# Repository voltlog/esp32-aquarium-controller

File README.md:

# ESP32 Aquarium/Terarrium Controller

This project started when a friend of mine which has a snake terrarium asked for my help to build a system that is capable of regulating temperature and humidity so the snake can live in optimum conditions. I’m not necessarily a snake lover, I would rather stay away from these kinds of creatures but that doesn’t stop me from helping my friend.

The ESP32 module is the core of this board and it serves as a central processor taking in sensor data and deciding when to switch on/off the 4 relay controlled outputs to adjust the environment inside the aquarium/terrarium.

If you would like to order one of these boards ready assembled, check out my [Tindie store](https://www.tindie.com/products/voltlog/esp32-aquarium-terrarium-controller/).

More info about this project in [Voltlog #361](https://youtu.be/Hlmbx2yu9M0).

Known issues in revA:
- Power brick module footprint is wrong so it needs to be installed on the bottom side of the board. 
- There are no mounting holes.
- Fitting the board inside the intended enclosure required some adjustments on the round cutouts. This is something to consider if you want to use the same enclosure but if you plan to install this in a larger plastic enclosure, it shouldn't be a problem.

## Firmware
Firmware is built as a PlatformIO project on the Arduino platform using publicly available open-source libraries. The HTML page servered by the asyncronous web server needs to be loaded into the ESP32 SPIFFS memory using the standard upload procedure. The code is just a proof of concept and is provided AS IS without warranty of any kind.

## Safety Warning
This control board uses mains voltage so you need to know what you are doing, otherwise, there is a high risk of electrical shock and/or fire. This is a serious topic, if you are not sure what you are doing, ask for help from an electrician. Every connection should be double checked before applying mains power.

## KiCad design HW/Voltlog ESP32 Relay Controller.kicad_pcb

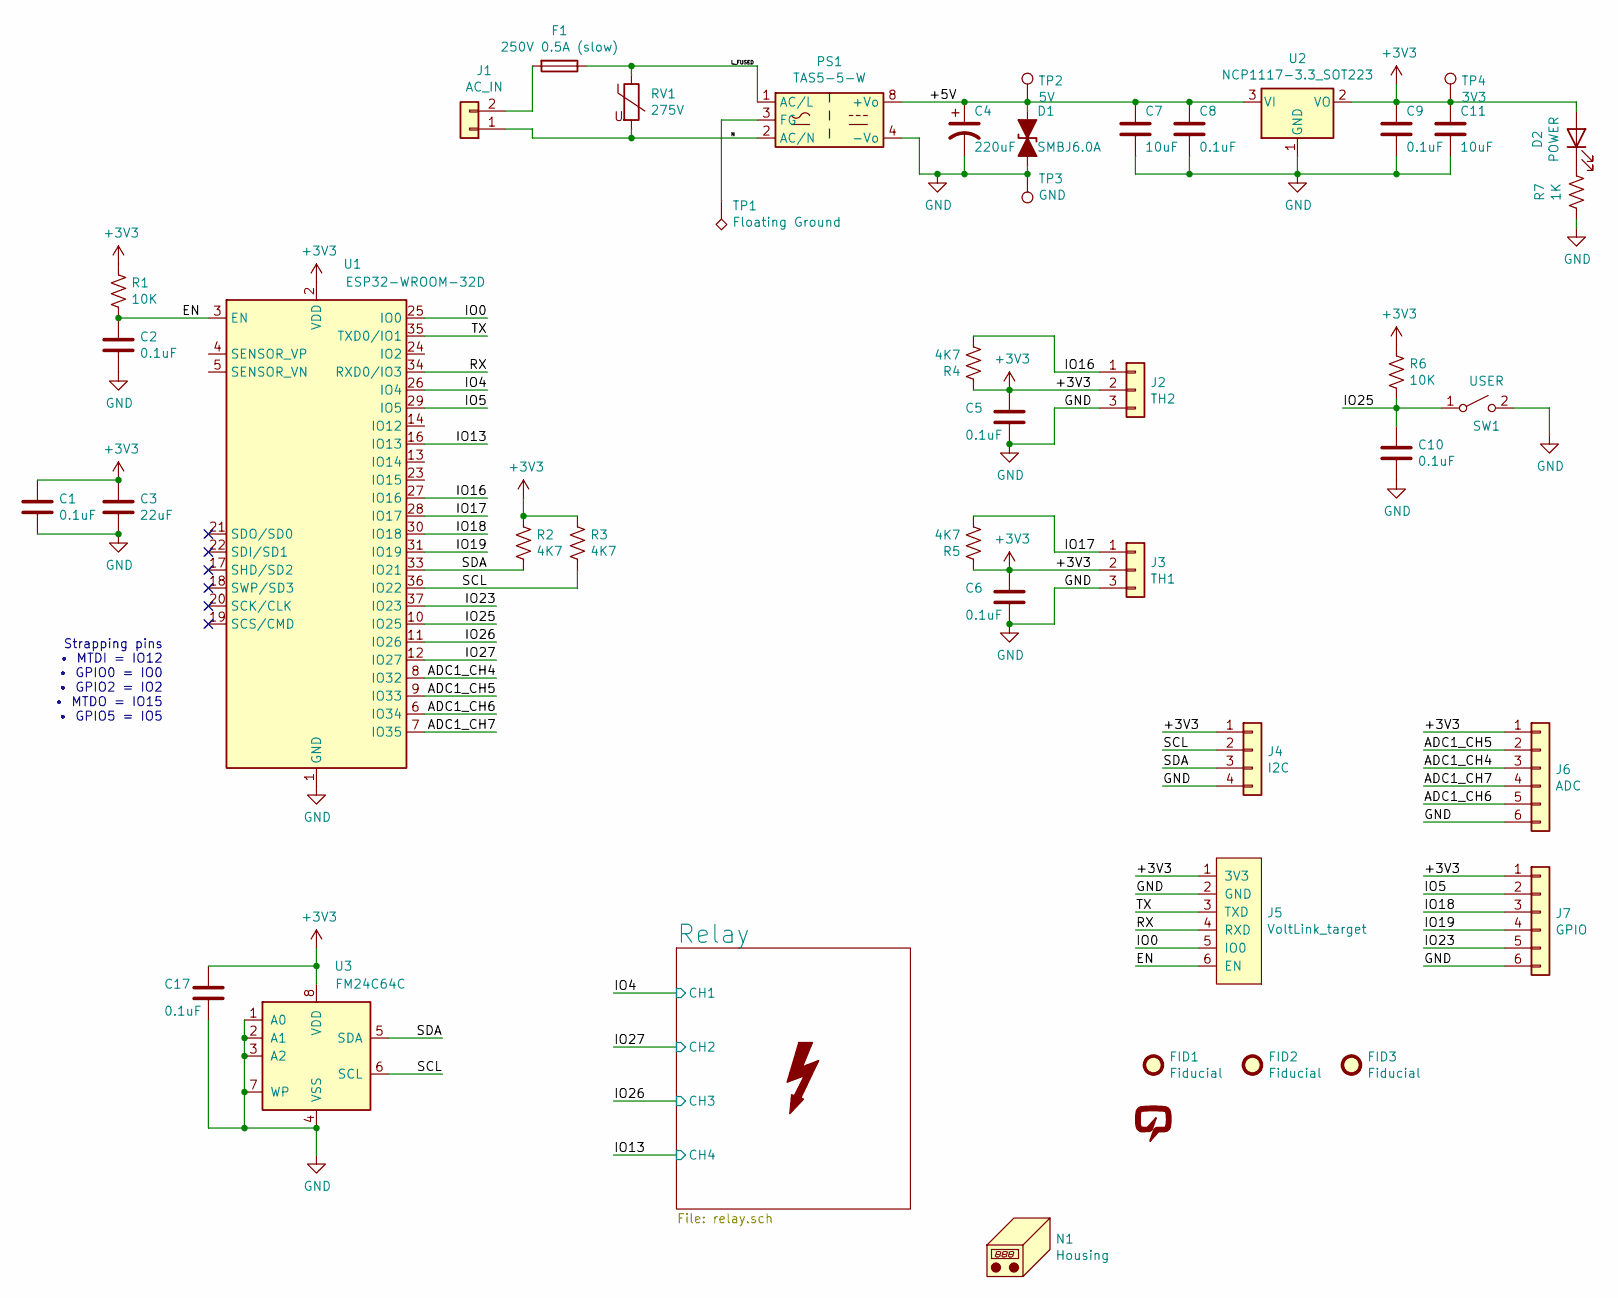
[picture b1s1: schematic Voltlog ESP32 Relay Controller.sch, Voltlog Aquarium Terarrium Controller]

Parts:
C1, C2, C5, C6, C8, C9, C10, C17: 0.1uF; C_0805_2012Metric
C3: 22uF; C_1206_3216Metric
C4: 220uF; CP_Elec_8x10.5; Voltage 25V
C7, C11: 10uF; C_0805_2012Metric
D1: SMBJ6.0A; D_SMB
D2: POWER; LED_0805_2012Metric
F1: 250V 0.5A (slow); Fuseholder_Cylinder-5x20mm_Stelvio-Kontek_PTF78_Horizontal_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
FID1, FID2, FID3: Fiducial; Fiducial_0.5mm_Mask1mm
J1: AC_IN; TerminalBlock_RND_205-00287_1x02_P5.08mm_Horizontal
J2: TH2; TerminalBlock_RND_205-00233_1x03_P5.08mm_Horizontal
J3: TH1; TerminalBlock_RND_205-00233_1x03_P5.08mm_Horizontal
J4: I2C; PinHeader_1x04_P2.54mm_Vertical
J5: VoltLink_target; VoltLink
J6: ADC; PinHeader_1x06_P2.54mm_Vertical
J7: GPIO; PinHeader_1x06_P2.54mm_Vertical
N1: Housing; Bernic_BE4969842011
PS1: TAS5-5-W; TDPOWER-TAS5
R1, R6: 10K; R_0805_2012Metric
R2, R3, R4, R5: 4K7; R_0805_2012Metric
R7: 1K; R_0805_2012Metric
RV1: 275V; RV_Disc_D12mm_W5mm_P7.5mm
SW1: USER; SW_SPST_PTS645
TP1: Floating Ground; SolderWirePad_1x01_SMD_5x10mm
TP2: 5V; TestPoint_Pad_D1.0mm
TP3: GND; TestPoint_Pad_D1.0mm
TP4: 3V3; TestPoint_Pad_D1.0mm
U1: ESP32-WROOM-32D; ESP32-WROOM-32
U2: NCP1117-3.3_SOT223; SOT-223-3_TabPin2
U3: FM24C64C; SOIC-8_3.9x4.9mm_P1.27mm
V1: VOLTLOG_LOGO; voltlog_mask_5mm

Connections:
+3V3: C1.1, C3.1, C5.1, C6.1, C9.1, C11.1, C17.1, D2.2 (A), J2.2, J3.2, J4.1, J5.1 (3V3), J6.1, J7.1, R1.1, R2.1, R3.1, R4.1, R5.1, R6.1, TP4.1, U1.2 (VDD), U2.2 (VO), U3.8 (VDD)
+5V: C4.1, C7.1, C8.1, D1.1 (A1), PS1.8 (+Vo), TP2.1, U2.3 (VI); also elsewhere on the board
/ADC1_CH4: J6.3, U1.8 (IO32)
/ADC1_CH5: J6.2, U1.9 (IO33)
/ADC1_CH6: J6.5, U1.6 (IO34)
/ADC1_CH7: J6.4, U1.7 (IO35)
/EN: C2.1, J5.6 (EN), R1.2, U1.3 (EN)
/IO0: J5.5 (IO0), U1.25 (IO0)
/IO2: U1.24 (IO2)
/IO4: U1.26 (IO4); also elsewhere on the board
/IO5: J7.2, U1.29 (IO5)
/IO13: U1.16 (IO13); also elsewhere on the board
/IO16: J2.1, R4.2, U1.27 (IO16)
/IO17: J3.1, R5.2, U1.28 (IO17)
/IO18: J7.3, U1.30 (IO18)
/IO19: J7.4, U1.31 (IO19)
/IO23: J7.5, U1.37 (IO23)
/IO25: C10.1, R6.2, SW1.1 (A), U1.10 (IO25)
/IO26: U1.11 (IO26); also elsewhere on the board
/IO27: U1.12 (IO27); also elsewhere on the board
/L_FUSED: F1.1, PS1.1 (AC/L), RV1.1
/N: J1.1, PS1.2 (AC/N), RV1.2
/RX: J5.4 (RXD), U1.34 (RXD0/IO3)
/SCL: J4.2, R3.2, U1.36 (IO22), U3.6 (SCL)
/SDA: J4.3, R2.2, U1.33 (IO21), U3.5 (SDA)
/TX: J5.3 (TXD), U1.35 (TXD0/IO1)
GND: C1.2, C2.2, C3.2, C4.2, C5.2, C6.2, C7.2, C8.2, C9.2, C10.2, C11.2, C17.2, D1.2 (A2), J2.3, J3.3, J4.4, J5.2 (GND), J6.6, J7.6, PS1.4 (-Vo), R7.2, SW1.2 (B), TP3.1, U1.1 (GND), U1.15 (GND), U1.38 (GND), U1.39 (GND), U2.1 (GND), U3.1 (A0), U3.2 (A1), U3.3 (A2), U3.4 (VSS), U3.7 (WP); also elsewhere on the board
unnamed: D2.1 (K), R7.1
unnamed: F1.2, J1.2
unnamed: PS1.3 (FG), TP1.1

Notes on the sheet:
Strapping pins • MTDI = IO12 • GPIO0 = IO0 • GPIO2 = IO2 • MTDO = IO15 • GPIO5 = IO5

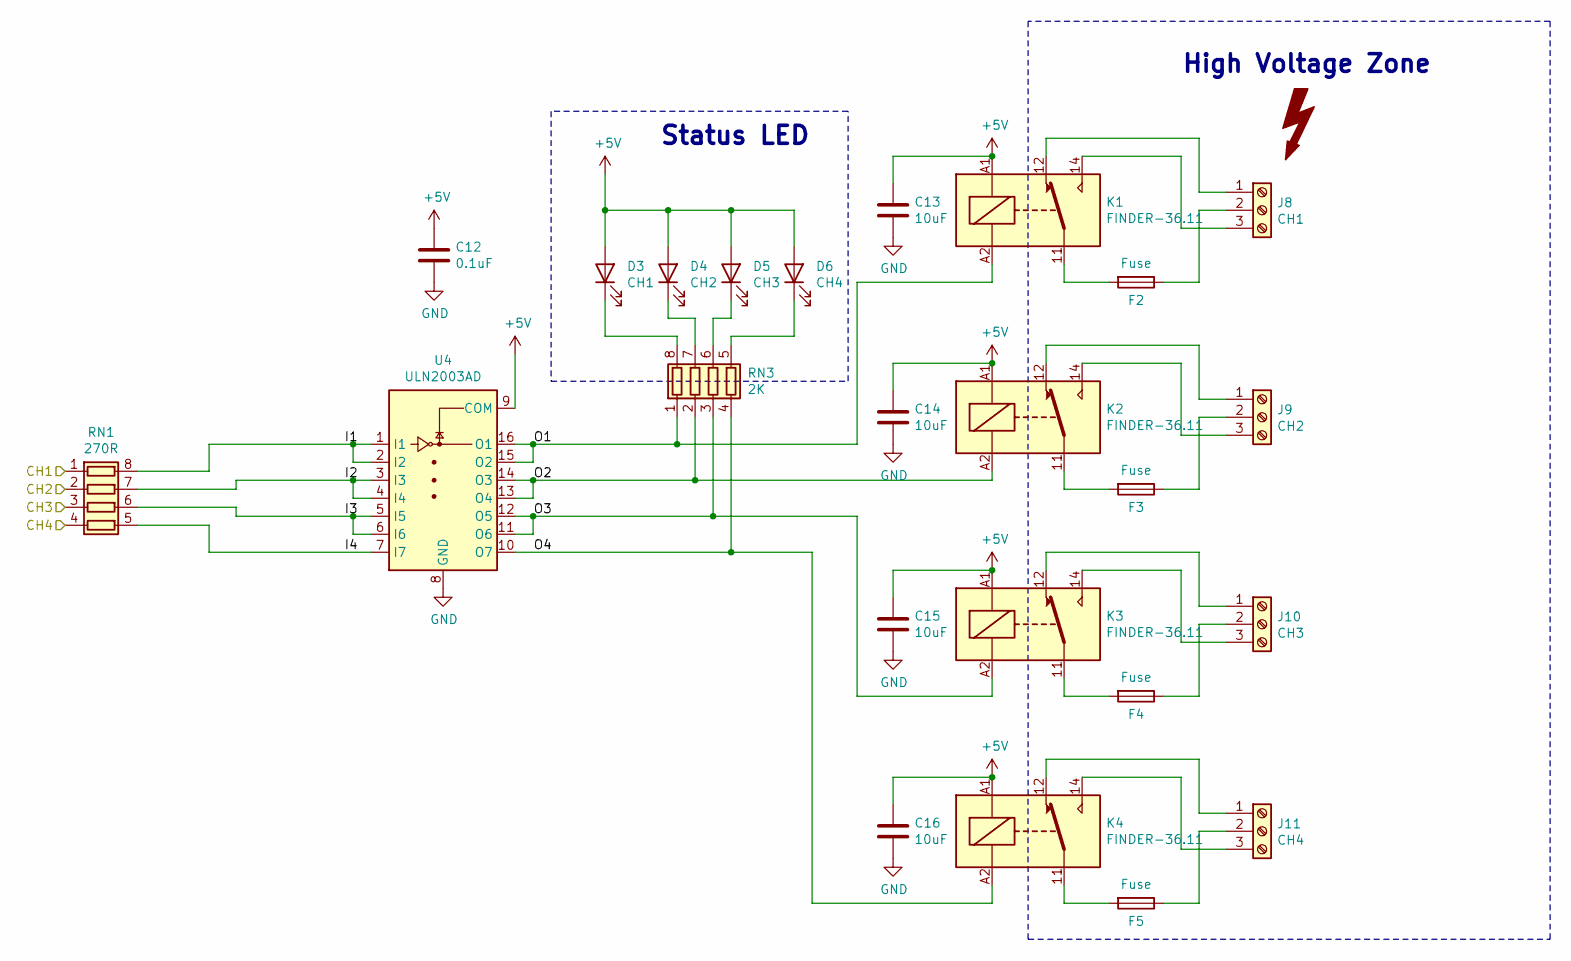
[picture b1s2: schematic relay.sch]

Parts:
C12: 0.1uF; C_0805_2012Metric
C13, C14, C15, C16: 10uF; C_0805_2012Metric
D3: CH1; LED_0805_2012Metric
D4: CH2; LED_0805_2012Metric
D5: CH3; LED_0805_2012Metric
D6: CH4; LED_0805_2012Metric
F2, F3, F4, F5: Fuse; Fuseholder_Cylinder-5x20mm_Stelvio-Kontek_PTF78_Horizontal_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
J8: CH1; TerminalBlock_Phoenix_MKDS-3-3-5.08_1x03_P5.08mm_Horizontal
J9: CH2; TerminalBlock_Phoenix_MKDS-3-3-5.08_1x03_P5.08mm_Horizontal
J10: CH3; TerminalBlock_Phoenix_MKDS-3-3-5.08_1x03_P5.08mm_Horizontal
J11: CH4; TerminalBlock_Phoenix_MKDS-3-3-5.08_1x03_P5.08mm_Horizontal
K1, K2, K3, K4: FINDER-36.11; Relay_SPDT_Finder_36.11
RN1: 270R; R_Array_Convex_4x0603
RN3: 2K; R_Array_Convex_4x0603
U4: ULN2003AD; SO-16_3.9x9.9mm_P1.27mm

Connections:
+5V: C12.1, C13.2, C14.2, C15.2, C16.2, D3.2 (A), D4.2 (A), D5.2 (A), D6.2 (A), K1.A1, K2.A1, K3.A1, K4.A1, U4.9 (COM); also elsewhere on the board
/IO4: RN1.1 (R1.1); also elsewhere on the board
/IO13: RN1.4 (R4.1); also elsewhere on the board
/IO26: RN1.3 (R3.1); also elsewhere on the board
/IO27: RN1.2 (R2.1); also elsewhere on the board
/Relay/I1: RN1.8 (R1.2), U4.1 (I1), U4.2 (I2)
/Relay/I2: RN1.7 (R2.2), U4.3 (I3), U4.4 (I4)
/Relay/I3: RN1.6 (R3.2), U4.5 (I5), U4.6 (I6)
/Relay/I4: RN1.5 (R4.2), U4.7 (I7)
/Relay/O1: K1.A2, RN3.1 (R1.1), U4.15 (O2), U4.16 (O1)
/Relay/O2: K2.A2, RN3.2 (R2.1), U4.13 (O4), U4.14 (O3)
/Relay/O3: K3.A2, RN3.3 (R3.1), U4.11 (O6), U4.12 (O5)
/Relay/O4: K4.A2, RN3.4 (R4.1), U4.10 (O7)
GND: C12.2, C13.1, C14.1, C15.1, C16.1, U4.8 (GND); also elsewhere on the board
unnamed: D3.1 (K), RN3.8 (R1.2)
unnamed: D4.1 (K), RN3.7 (R2.2)
unnamed: D5.1 (K), RN3.6 (R3.2)
unnamed: D6.1 (K), RN3.5 (R4.2)
unnamed: F2.1, J8.2
unnamed: F2.2, K1.11
unnamed: F3.1, J9.2
unnamed: F3.2, K2.11
unnamed: F4.1, J10.2
unnamed: F4.2, K3.11
unnamed: F5.1, J11.2
unnamed: F5.2, K4.11
unnamed: J8.1, K1.12
unnamed: J8.3, K1.14
unnamed: J9.1, K2.12
unnamed: J9.3, K2.14
unnamed: J10.1, K3.12
unnamed: J10.3, K3.14
unnamed: J11.1, K4.12
unnamed: J11.3, K4.14

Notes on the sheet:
High Voltage Zone
Status LED

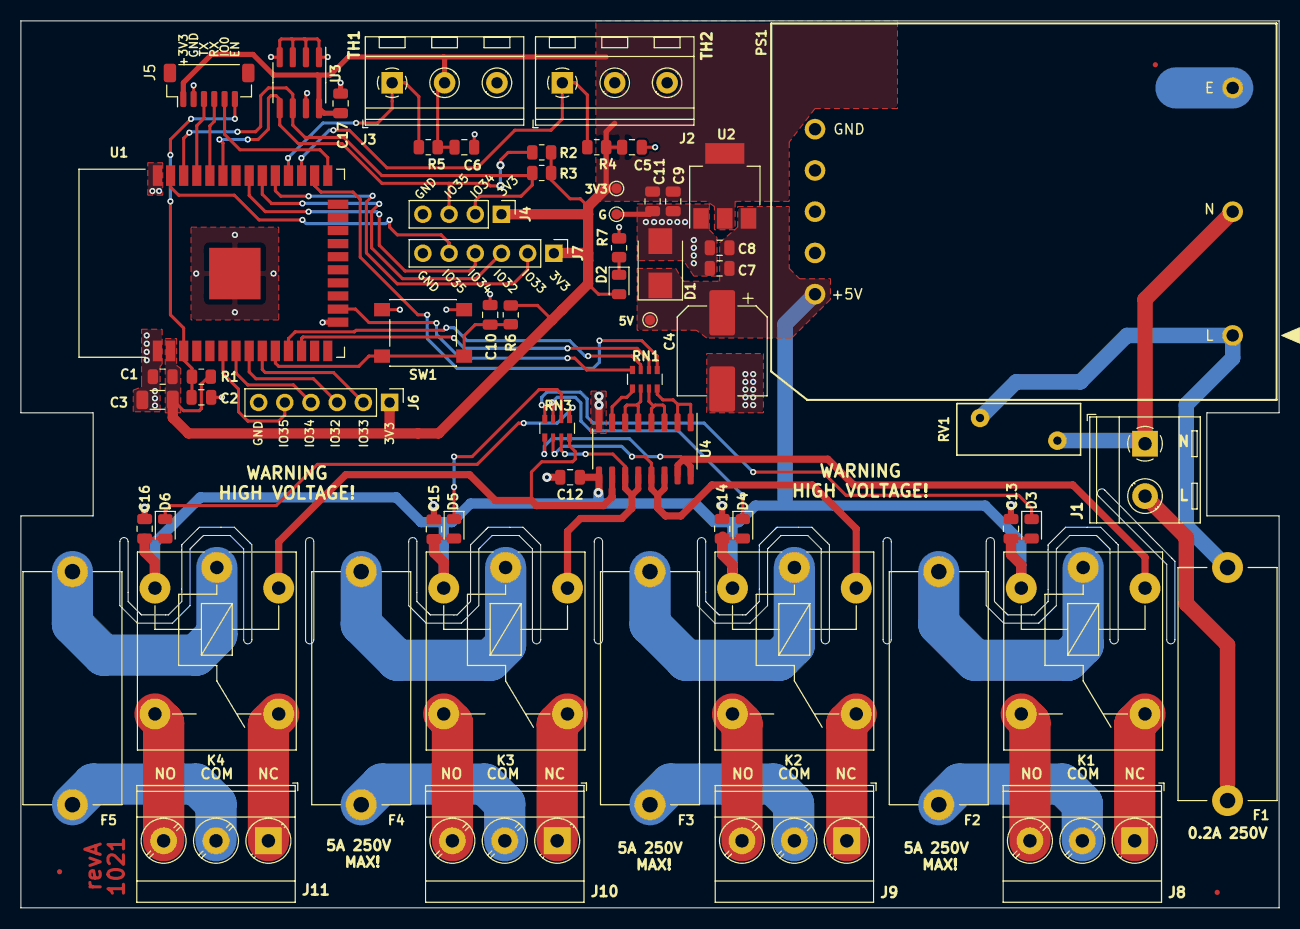
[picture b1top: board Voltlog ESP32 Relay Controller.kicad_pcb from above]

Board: 2 copper layers, 122.0 x 86.0 mm, 68 parts (1 on the bottom side), 57 nets.

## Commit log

2021-04-19 Added HW source files

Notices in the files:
HW/Voltlog ESP32 Relay Controller.sch:
License: GPLv3
